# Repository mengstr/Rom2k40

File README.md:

# Rom2k40
## Please note! This is currently a WIP

This is a EPROM emulator that supports standard EPROM in sizes from the 2716 up to 27512. Upload of new contents into the emulated EPROM is done over a serial link.

Emulating 2716 and 2732 which are 24-pin devices requires a solder jumper at the bottom to be bridged to power the board with +5v from the correct pin.

The USB of the RP2040 is not connected so the firmware must be uploaded over the SWD interface that is broken out into the same connector as the serial port.

The two rows of 14-pin headers that goes to the target board does NOT have a standard 600mil distance! Since standard sockets can't take the regular square pinheader pins I've designed this board to have the pinheaders to be soldered ontop of a real 28-pin device, like a broken/bas EPROM or any other 28-pin DIP. It probably works best using an EPROM since the bond wires to the die of the chip must be severed.  I'm not sure how it would be done on another type of chip, but if it's plastic it could be possible to just drill a hole in the middle straight through it and then check that all pins are is isolated from eachother.

### PCB specs

The PCB is 40 x 19mm (1.6 x 0.75") using a four layer PCB with 0.2mm vias having a 0.2mm annular ring giving a total ring size of 0.6mm. Track with/spacing is mostly 125/125um (4.9 mil). This is in accordance to the Aisler 4-layer specification.

### Schematic

[PDF schematic availabe here](https://github.com/mengstr/Rom2k40/raw/main/Images/Rom2k40.pdf)

### Bill of materials and substitutions

Interactive [BOM](http://htmlpreview.github.io/?https://github.com/mengstr/Rom2k40/blob/main/Bom/ibom.html)

The MOSFET transistor could probably be replaced with a 2N7002 with a bit of luck, but they can be hard to drive fully from a 3.3 volt device.

The 3.3 volt VREG could be replaced with any other device with a similar pinout and a output current of 150mA (needs to be verified).

The FLASH memory could br replaced with any SO-8 device that is compatible with the RP2040 and also have enough memory for both the emulated EPROM and the firmware. Since a 27512 is the largest EPROM emulated a 1Mbit FLASh should be suffice. I can't imagine that the firmware will take more than 64Kbyte.

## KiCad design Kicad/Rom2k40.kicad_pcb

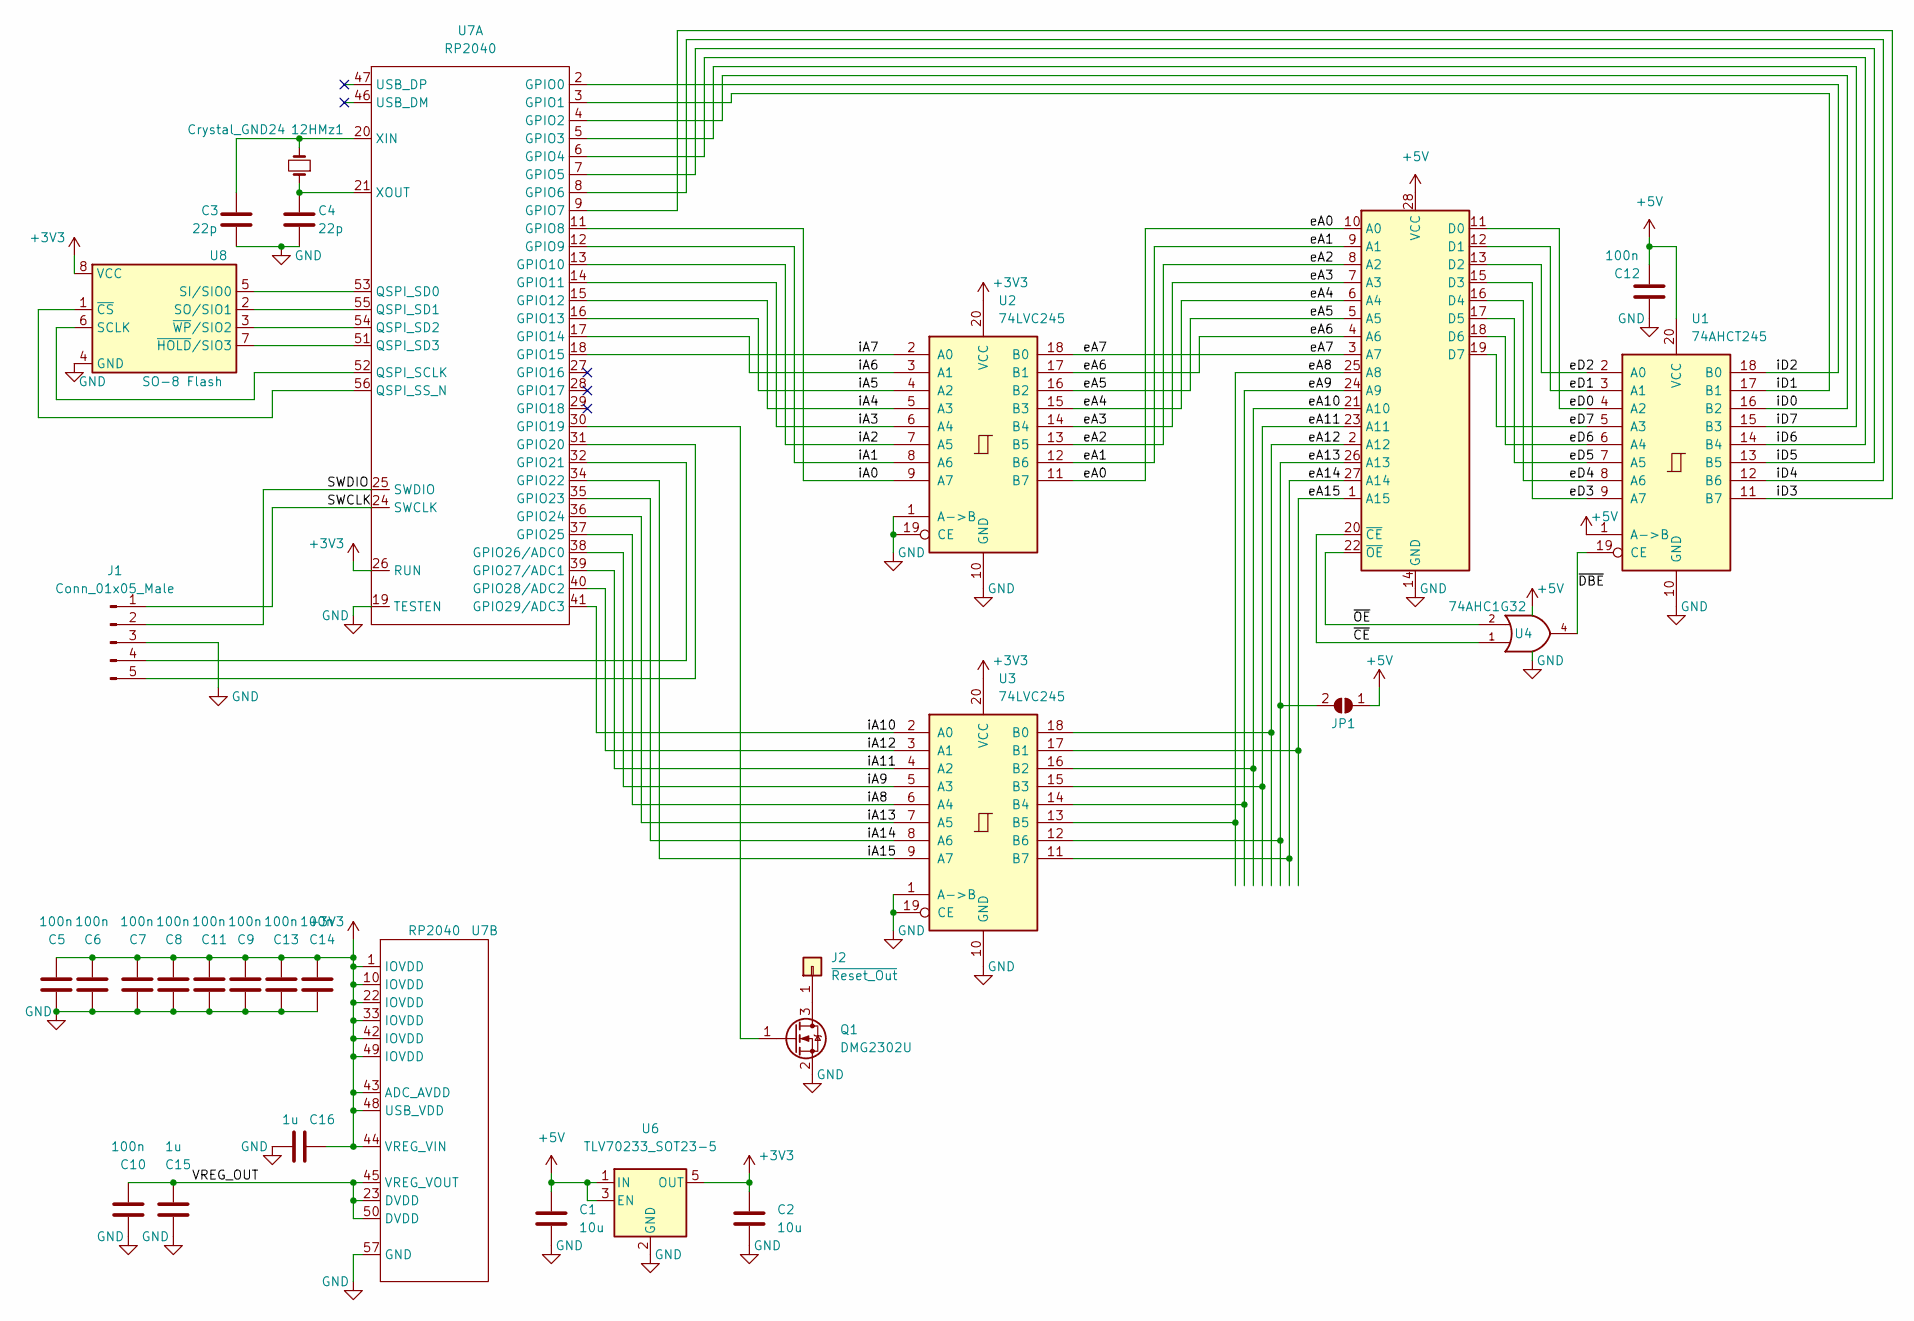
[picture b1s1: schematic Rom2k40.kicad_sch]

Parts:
12HMz1: Crystal_GND24; Crystal_HC49-U_Vertical
C1, C2: 10u; C_0805_2012Metric
C3, C4: 22p; C_0603_1608Metric
C5, C6, C7, C8, C9, C10, C11, C12, C13, C14: 100n; C_0603_1608Metric
C15, C16: 1u; C_0603_1608Metric
J1: Conn_01x05_Male; PinHeader_1x05_P2.54mm_Vertical
J2: ~{Reset_Out}; PinHeader_1x01_P2.54mm_Vertical
J3: 2x14 pinheader; DIP-28_Piggyback
JP1: SolderJumper_2_Open; SolderJumper-2_P1.3mm_Open_RoundedPad1.0x1.5mm
Q1: DMG2302U; TSOT-23
U1: 74AHCT245; TSSOP-20_4.4x6.5mm_P0.65mm
U2, U3: 74LVC245; TSSOP-20_4.4x6.5mm_P0.65mm
U4: 74AHC1G32; TSOT-23-5
U6: TLV70233_SOT23-5; SOT-23-5
U7: RP2040; QFN-56-1EP_7x7mm_P0.4mm_Pad3.2_Handsolder
U8: SO-8 Flash; SOP-8_3.9x4.9mm_P1.27mm

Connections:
+3V3: C2.1, C5.1, C6.1, C7.1, C8.1, C9.1, C11.1, C13.1, C14.1, C16.1, U2.20 (VCC), U3.20 (VCC), U6.5 (OUT), U7.1 (IOVDD), U7.10 (IOVDD), U7.22 (IOVDD), U7.26 (RUN), U7.33 (IOVDD), U7.42 (IOVDD), U7.43 (ADC_AVDD), U7.44 (VREG_VIN), U7.48 (USB_VDD), U7.49 (IOVDD), U8.8 (VCC)
+5V: C1.1, C12.1, J3.28 (VCC), JP1.1 (A), U1.1 (A->B), U1.20 (VCC), U4.5 (VCC), U6.1 (IN), U6.3 (EN)
/SWCLK: J1.1, U7.24 (SWCLK)
/SWDIO: J1.2, U7.25 (SWDIO)
/VREG_OUT: C10.1, C15.1, U7.23 (DVDD), U7.45 (VREG_VOUT), U7.50 (DVDD)
/eA0: J3.10 (A0), U2.11 (B7)
/eA1: J3.9 (A1), U2.12 (B6)
/eA2: J3.8 (A2), U2.13 (B5)
/eA3: J3.7 (A3), U2.14 (B4)
/eA4: J3.6 (A4), U2.15 (B3)
/eA5: J3.5 (A5), U2.16 (B2)
/eA6: J3.4 (A6), U2.17 (B1)
/eA7: J3.3 (A7), U2.18 (B0)
/eA8: J3.25 (A8), U3.13 (B5)
/eA9: J3.24 (A9), U3.14 (B4)
/eA10: J3.21 (A10), U3.16 (B2)
/eA11: J3.23 (A11), U3.15 (B3)
/eA12: J3.2 (A12), U3.18 (B0)
/eA13: J3.26 (A13), JP1.2 (B), U3.12 (B6)
/eA14: J3.27 (A14), U3.11 (B7)
/eA15: J3.1 (A15), U3.17 (B1)
/eD0: J3.11 (D0), U1.4 (A2)
/eD1: J3.12 (D1), U1.3 (A1)
/eD2: J3.13 (D2), U1.2 (A0)
/eD3: J3.15 (D3), U1.9 (A7)
/eD4: J3.16 (D4), U1.8 (A6)
/eD5: J3.17 (D5), U1.7 (A5)
/eD6: J3.18 (D6), U1.6 (A4)
/eD7: J3.19 (D7), U1.5 (A3)
/iA0: U2.9 (A7), U7.11 (GPIO8)
/iA1: U2.8 (A6), U7.12 (GPIO9)
/iA2: U2.7 (A5), U7.13 (GPIO10)
/iA3: U2.6 (A4), U7.14 (GPIO11)
/iA4: U2.5 (A3), U7.15 (GPIO12)
/iA5: U2.4 (A2), U7.16 (GPIO13)
/iA6: U2.3 (A1), U7.17 (GPIO14)
/iA7: U2.2 (A0), U7.18 (GPIO15)
/iA8: U3.6 (A4), U7.37 (GPIO25)
/iA9: U3.5 (A3), U7.38 (GPIO26/ADC0)
/iA10: U3.2 (A0), U7.41 (GPIO29/ADC3)
/iA11: U3.4 (A2), U7.39 (GPIO27/ADC1)
/iA12: U3.3 (A1), U7.40 (GPIO28/ADC2)
/iA13: U3.7 (A5), U7.36 (GPIO24)
/iA14: U3.8 (A6), U7.35 (GPIO23)
/iA15: U3.9 (A7), U7.34 (GPIO22)
/iD0: U1.16 (B2), U7.4 (GPIO2)
/iD1: U1.17 (B1), U7.3 (GPIO1)
/iD2: U1.18 (B0), U7.2 (GPIO0)
/iD3: U1.11 (B7), U7.9 (GPIO7)
/iD4: U1.12 (B6), U7.8 (GPIO6)
/iD5: U1.13 (B5), U7.7 (GPIO5)
/iD6: U1.14 (B4), U7.6 (GPIO4)
/iD7: U1.15 (B3), U7.5 (GPIO3)
/~CE: J3.20 (~CE), U4.1
/~DBE: U1.19 (CE), U4.4
/~OE: J3.22 (~OE), U4.2
GND: C1.2, C2.2, C3.1, C4.1, C5.2, C6.2, C7.2, C8.2, C9.2, C10.2, C11.2, C12.2, C13.2, C14.2, C15.2, C16.2, J1.3, J3.14 (GND), Q1.2 (S), U1.10 (GND), U2.1 (A->B), U2.10 (GND), U2.19 (CE), U3.1 (A->B), U3.10 (GND), U3.19 (CE), U4.3 (GND), U6.2 (GND), U7.19 (TESTEN), U7.57 (GND), U8.4 (GND)
unnamed: 12HMz1.1, C4.2, U7.21 (XOUT)
unnamed: 12HMz1.2, C3.2, U7.20 (XIN)
unnamed: J1.4, U7.32 (GPIO21)
unnamed: J1.5, U7.31 (GPIO20)
unnamed: J2.1, Q1.3 (D)
unnamed: Q1.1 (G), U7.30 (GPIO19)
unnamed: U7.51 (QSPI_SD3), U8.7 (~HOLD/SIO3)
unnamed: U7.52 (QSPI_SCLK), U8.6 (SCLK)
unnamed: U7.53 (QSPI_SD0), U8.5 (SI/SIO0)
unnamed: U7.54 (QSPI_SD2), U8.3 (~WP/SIO2)
unnamed: U7.55 (QSPI_SD1), U8.2 (SO/SIO1)
unnamed: U7.56 (QSPI_SS_N), U8.1 (~CS)

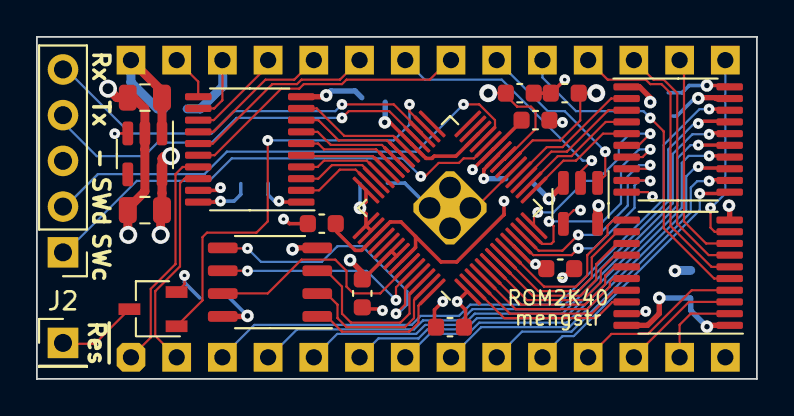
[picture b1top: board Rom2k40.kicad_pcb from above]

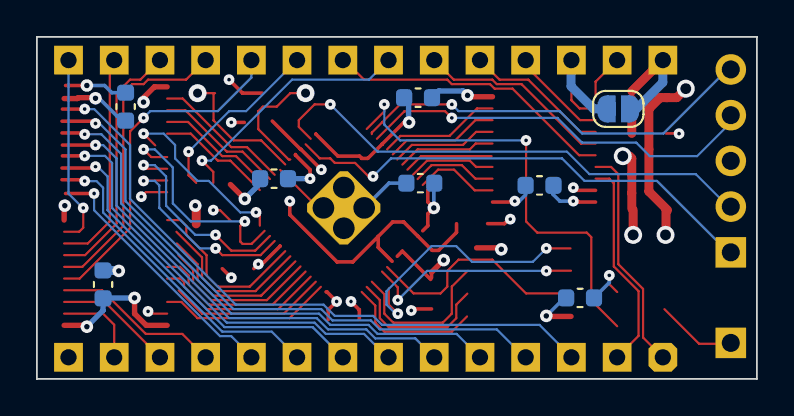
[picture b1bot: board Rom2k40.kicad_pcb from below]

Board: 4 copper layers, 40.0 x 19.0 mm, 28 parts (8 on the bottom side), 69 nets.

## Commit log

2022-08-13 Update README. Add EPROM pinout to sch
2022-08-13 Move schematic pdf
